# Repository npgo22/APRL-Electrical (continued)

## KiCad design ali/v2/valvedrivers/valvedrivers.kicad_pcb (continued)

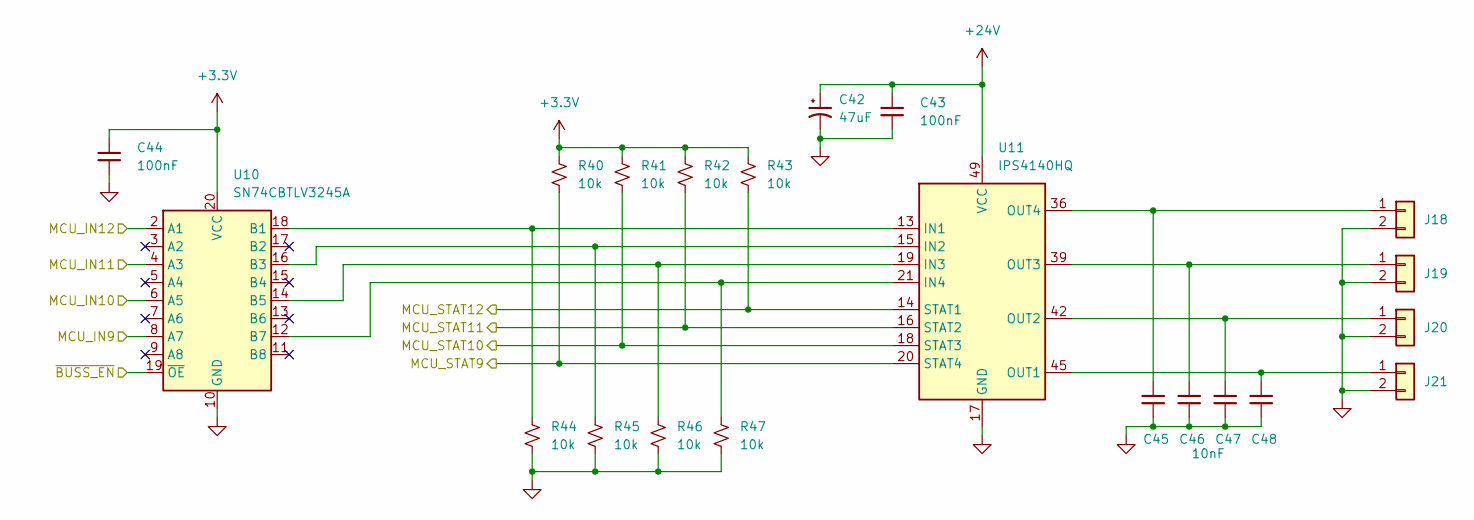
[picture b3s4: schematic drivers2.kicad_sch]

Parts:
C42: 47uF; KEMET MU VIB; MPN A767KS476M1JLAE036
C43, C44: 100nF; C_0603; MPN GRM188R72A104KA35
C45, C46, C47, C48: 10nF; C_0603; MPN GRM1885C1H103JA01
J18, J19, J20, J21: Conn_01x02; Molex_CLIK-Mate_503159-0201_1x02-1MP_P1.50mm_Vertical; MPN 503159-0201
R40, R41, R42, R43, R44, R45, R46, R47: 10k; R_0603; MPN RC0603FR-0710KL
U10: SN74CBTLV3245A; TSSOP-20_4.4x6.5mm_P0.65mm; MPN SN74CBTLV3245APWR
U11: IPS4140HQ; QFN-48_EP_9.01x7.01_Pitch0.5mm; MPN IPS4140HQ

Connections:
+3.3V: C44.1, R40.1, R41.1, R42.1, R43.1, U10.20 (VCC); also elsewhere on the board
+24V: C42.1, C43.1, U11.49 (VCC); also elsewhere on the board
/Driver Set 1/~BUSS_EN: U10.19 (~OE); also elsewhere on the board
/Driver Set 2/MCU_IN9: U10.8 (A7); also elsewhere on the board
/Driver Set 2/MCU_IN10: U10.6 (A5); also elsewhere on the board
/Driver Set 2/MCU_IN11: U10.4 (A3); also elsewhere on the board
/Driver Set 2/MCU_IN12: U10.2 (A1); also elsewhere on the board
/Driver Set 2/MCU_STAT9: R40.2, U11.20 (STAT4); also elsewhere on the board
/Driver Set 2/MCU_STAT10: R41.2, U11.18 (STAT3); also elsewhere on the board
/Driver Set 2/MCU_STAT11: R42.2, U11.16 (STAT2); also elsewhere on the board
/Driver Set 2/MCU_STAT12: R43.2, U11.14 (STAT1); also elsewhere on the board
GND: C42.2, C43.2, C44.2, C45.2, C46.2, C47.2, C48.2, J18.2, J19.2, J20.2, J21.2, R44.2, R45.2, R46.2, R47.2, U10.10 (GND), U11.17 (GND); also elsewhere on the board
unnamed: C45.1, J18.1, U11.36 (OUT4), U11.37 (OUT4), U11.38 (OUT4)
unnamed: C46.1, J19.1, U11.39 (OUT3), U11.40 (OUT3), U11.41 (OUT3)
unnamed: C47.1, J20.1, U11.42 (OUT2), U11.43 (OUT2), U11.44 (OUT2)
unnamed: C48.1, J21.1, U11.45 (OUT1), U11.46 (OUT1), U11.47 (OUT1)
unnamed: R44.1, U10.18 (B1), U11.13 (IN1)
unnamed: R45.1, U10.16 (B3), U11.15 (IN2)
unnamed: R46.1, U10.14 (B5), U11.19 (IN3)
unnamed: R47.1, U10.12 (B7), U11.21 (IN4)

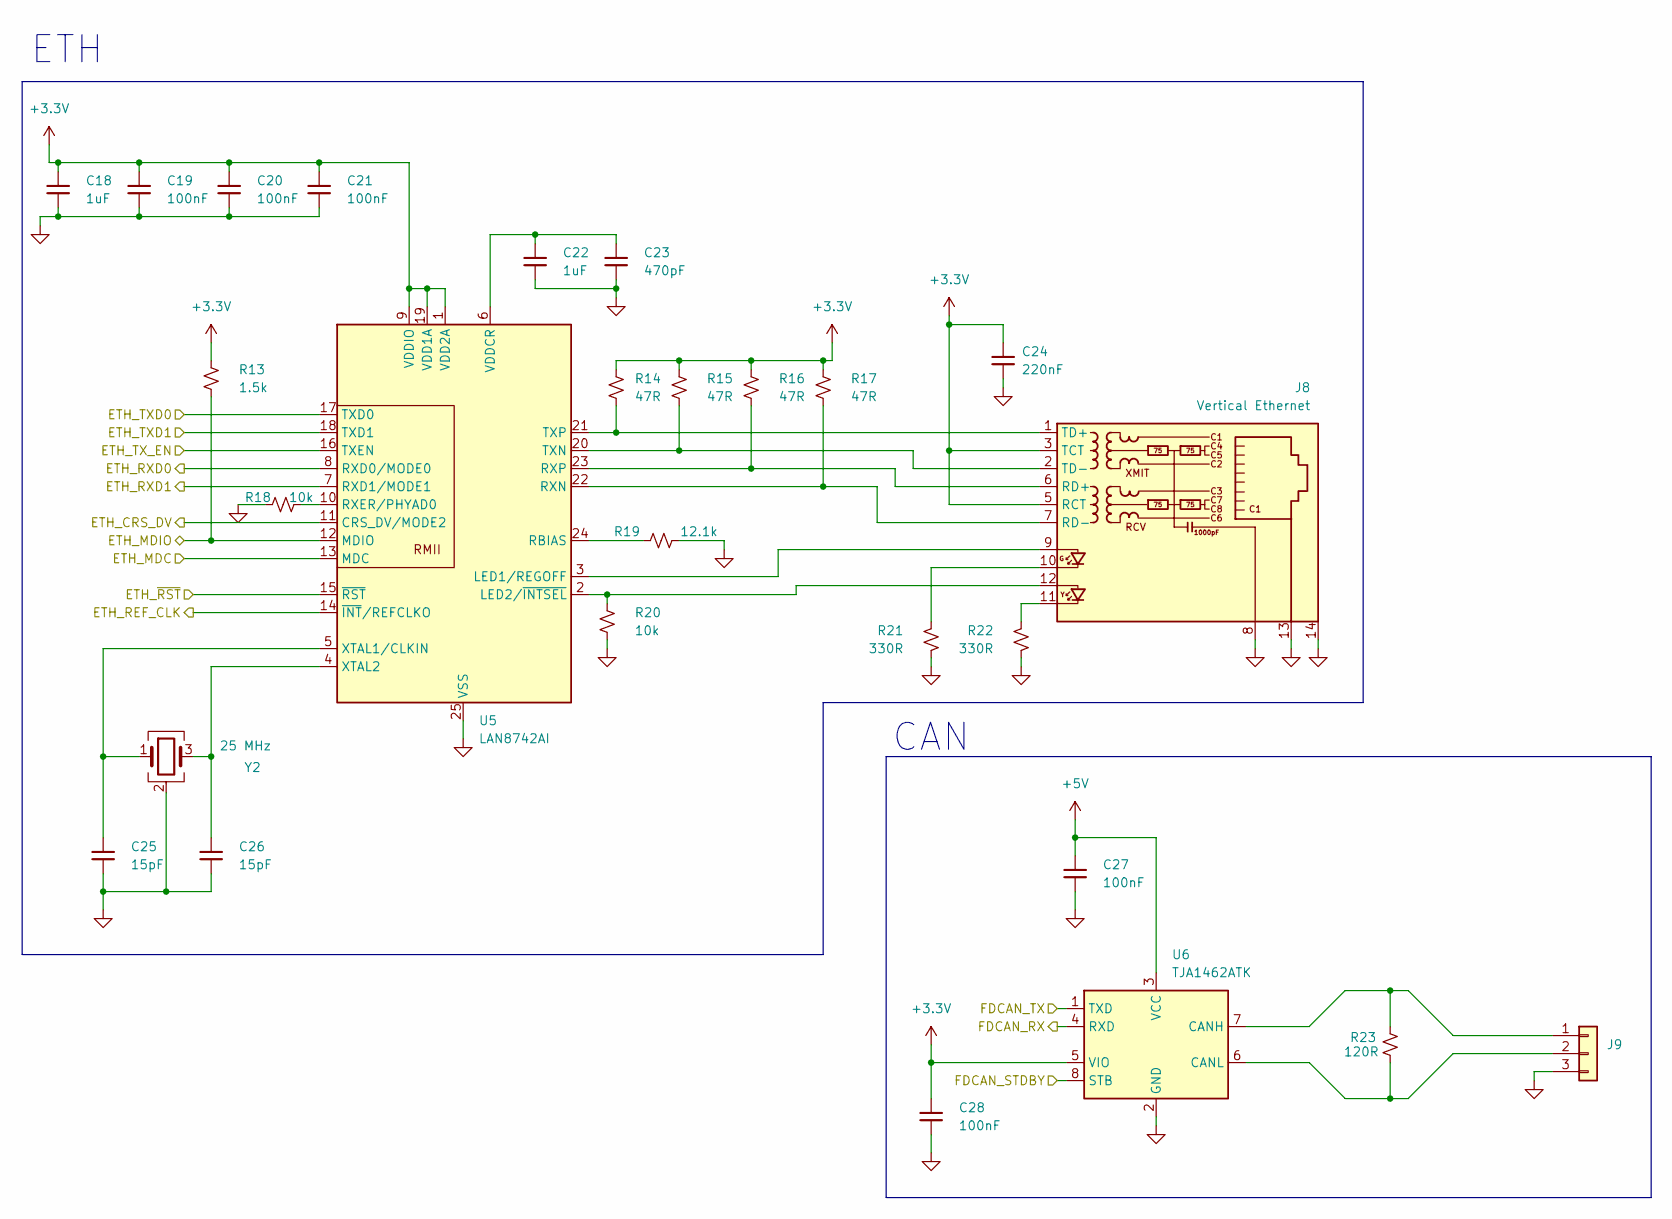
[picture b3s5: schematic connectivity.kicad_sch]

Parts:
C18, C22: 1uF; C_0603; MPN GRM188D72A105KE01
C19, C20, C21, C27, C28: 100nF; C_0603; MPN GRM188R72A104KA35
C23: 470pF; C_0603; MPN GRM1885C1H471JA01
C24: 220nF; C_0603; MPN GRM188R71H224KAC4
C25, C26: 15pF; C_0603; MPN GRM1885C2E150FW07
J8: Vertical Ethernet; RJ45_Hanrun_HY951180A_Vertical; MPN HY951180A
J9: Conn_01x03; Molex_CLIK-Mate_503159-0301_1x03-1MP_P1.50mm_Vertical; MPN 503159-0301
R13: 1.5k; R_0603; MPN RC0603FR-071K5L
R14, R15, R16, R17: 47R; R_0603; MPN RC0603FR-0747RL
R18, R20: 10k; R_0603; MPN RC0603FR-0710KL
R19: 12.1k; R_0603; MPN RT0603BRD0712K1L
R21, R22: 330R; R_0603; MPN RC0603FR-07330RL
R23: 120R; R_0603; MPN AC0603FR-07120RL
U5: LAN8742AI; VQFN-24-1EP_4x4mm_P0.5mm_EP2.5x2.5mm_ThermalVias; MPN LAN8742AI-CZ-TR
U6: TJA1462ATK; HVSON-8-1EP_3x3mm_P0.65mm_EP1.6x2.4mm_ThermalVias; MPN TJA1462ATK/0Z
Y2: 25 MHz; 3225-4P-L; MPN X1E0000210139

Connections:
+3.3V: C18.1, C19.1, C20.1, C21.1, C24.1, C28.1, J8.3 (TCT), J8.5 (RCT), R13.1, R14.1, R15.1, R16.1, R17.1, U5.1 (VDD2A), U5.9 (VDDIO), U5.19 (VDD1A), U6.5 (VIO); also elsewhere on the board
+5V: C27.1, U6.3 (VCC); also elsewhere on the board
/Connectivity/ETH_CRS_DV: U5.11 (CRS_DV/MODE2); also elsewhere on the board
/Connectivity/ETH_MDC: U5.13 (MDC); also elsewhere on the board
/Connectivity/ETH_MDIO: R13.2, U5.12 (MDIO); also elsewhere on the board
/Connectivity/ETH_REF_CLK: U5.14 (~INT/REFCLKO); also elsewhere on the board
/Connectivity/ETH_RXD0: U5.8 (RXD0/MODE0); also elsewhere on the board
/Connectivity/ETH_RXD1: U5.7 (RXD1/MODE1); also elsewhere on the board
/Connectivity/ETH_TXD0: U5.17 (TXD0); also elsewhere on the board
/Connectivity/ETH_TXD1: U5.18 (TXD1); also elsewhere on the board
/Connectivity/ETH_TX_EN: U5.16 (TXEN); also elsewhere on the board
/Connectivity/ETH_~RST: U5.15 (~RST); also elsewhere on the board
/Connectivity/FDCAN_RX: U6.4 (RXD); also elsewhere on the board
/Connectivity/FDCAN_STDBY: U6.8 (STB); also elsewhere on the board
/Connectivity/FDCAN_TX: U6.1 (TXD); also elsewhere on the board
GND: C18.2, C19.2, C20.2, C21.2, C22.2, C23.2, C24.2, C25.2, C26.2, C27.2, C28.2, J8.8, J8.13, J8.14, J9.3, R18.1, R19.2, R20.2, R21.2, R22.2, U5.25 (VSS), U6.2 (GND), U6.9 (GND), Y2.2 (G), Y2.4 (G); also elsewhere on the board
unnamed: J8.10, R21.1
unnamed: J8.11, R22.1
unnamed: J8.6 (RD+), R16.2, U5.23 (RXP)
unnamed: J8.7 (RD-), R17.2, U5.22 (RXN)
unnamed: J8.1 (TD+), R14.2, U5.21 (TXP)
unnamed: J8.2 (TD-), R15.2, U5.20 (TXN)
unnamed: J9.1, R23.2, U6.7 (CANH)
unnamed: J9.2, R23.1, U6.6 (CANL)
unnamed: J8.9, U5.3 (LED1/REGOFF)
unnamed: J8.12, R20.1, U5.2 (LED2/~INTSEL)
unnamed: R19.1, U5.24 (RBIAS)
unnamed: R18.2, U5.10 (RXER/PHYAD0)
unnamed: C22.1, C23.1, U5.6 (VDDCR)
unnamed: C25.1, U5.5 (XTAL1/CLKIN), Y2.1
unnamed: C26.1, U5.4 (XTAL2), Y2.3

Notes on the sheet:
ETH
CAN

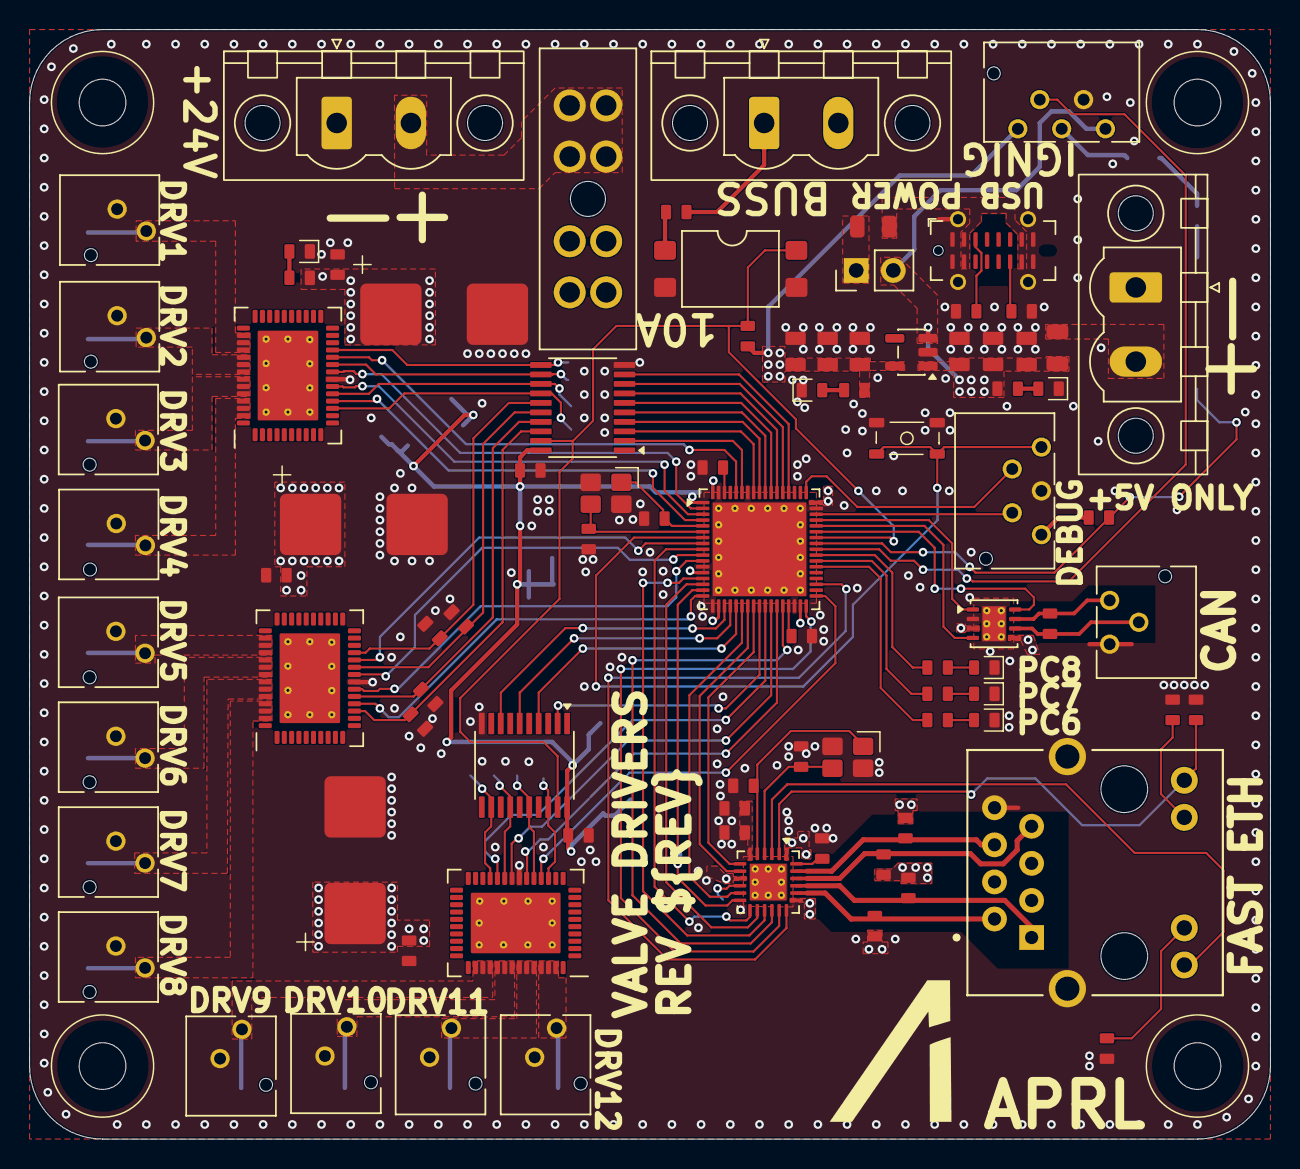
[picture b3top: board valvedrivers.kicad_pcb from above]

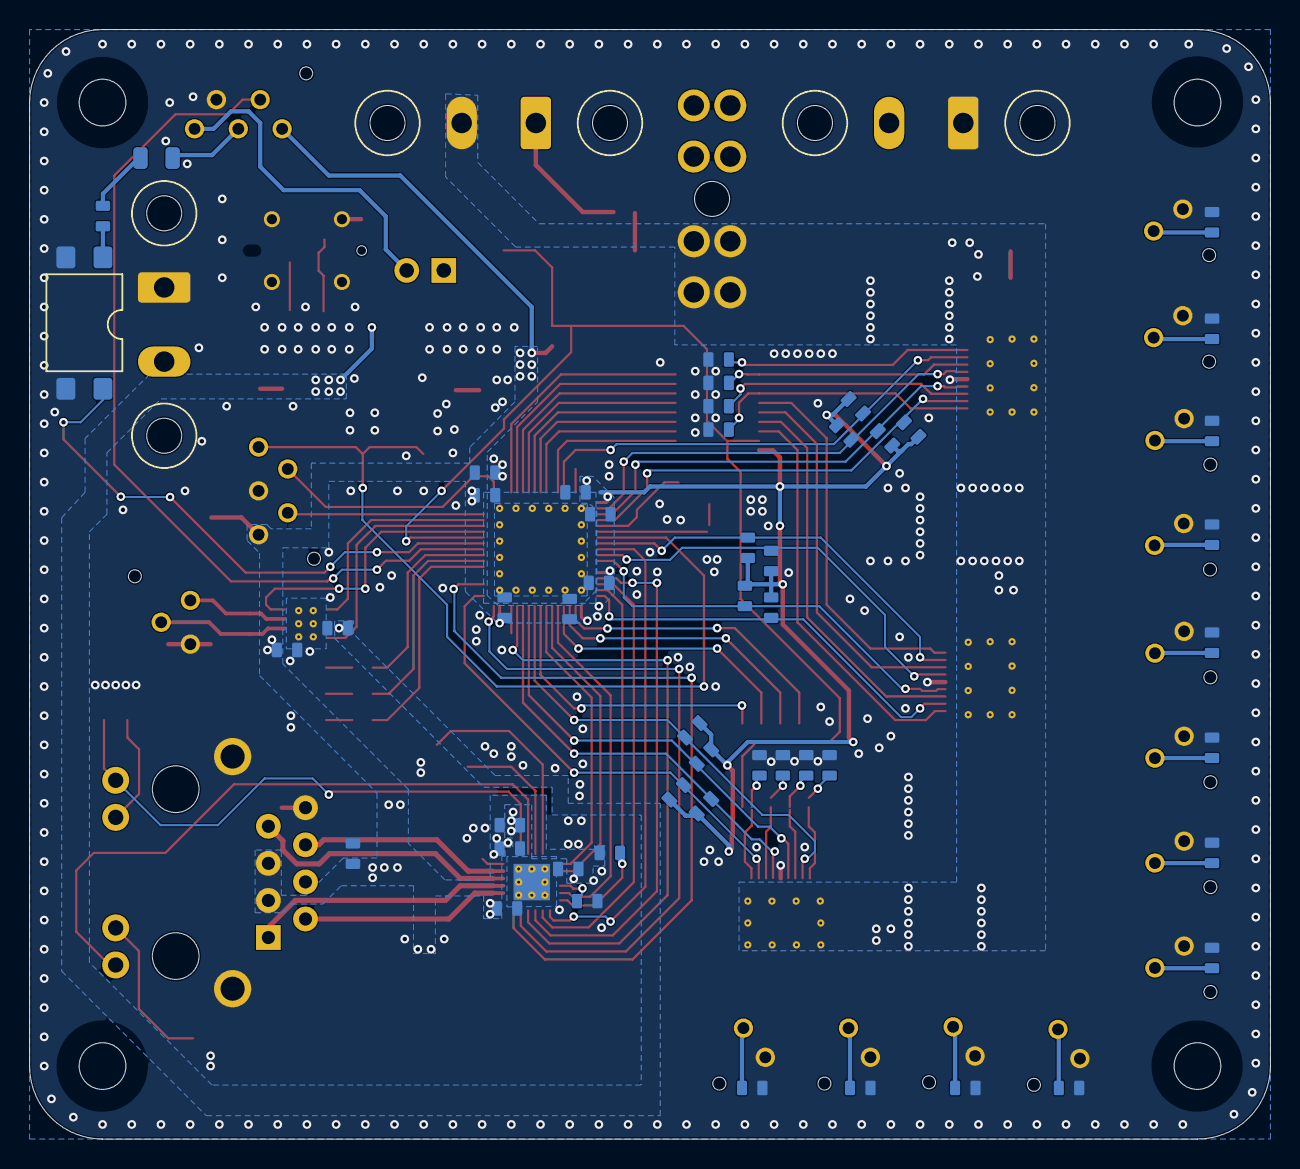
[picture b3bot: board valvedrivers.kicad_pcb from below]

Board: 4 copper layers, 85.0 x 76.0 mm, 144 parts (51 on the bottom side), 110 nets.

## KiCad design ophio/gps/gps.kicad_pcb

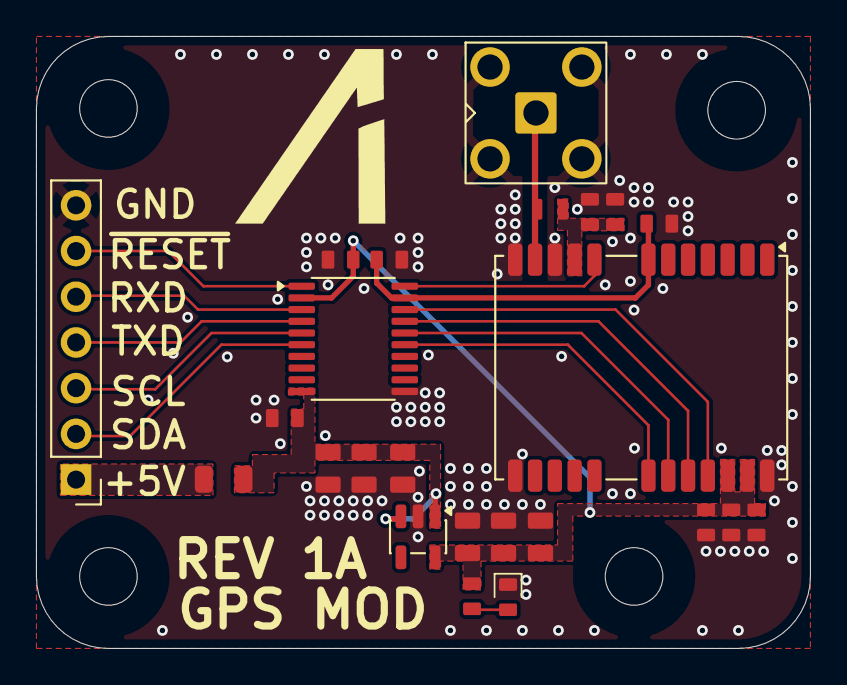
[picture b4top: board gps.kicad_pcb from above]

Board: 4 copper layers, 43.0 x 34.0 mm, 28 parts (0 on the bottom side), 18 nets.

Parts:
C1, C2, C3, C5, C7, C9: 22uF; C_0805
C4, C6, C8, C12, C14: 100nF; C_0603
C10, C11: 33pF; C_0603
C13: 100pF; C_0603
D1: LED_Small; LED_0603
F1: 100mA hold; Fuse_0805_2012Metric
H1, H2, H3, H4: MountingHole; MountingHole_3.2mm_M3
J1: Conn_01x07; PinHeader_1x07_P2.54mm_Vertical
J2: SMA; SMA_BAT_Wireless_BWSMA-KWE-Z001
L1: 68 nH; LQW18AN68NG8Z
R1, R2: 10k; R_0603
U1: AP2112K-3.3; SOT-23-5
U2: TXS0108EPW; TSSOP-20_4.4x6.5mm_P0.65mm
U3: LC29H; ublox_NEO

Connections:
+2.8V: C6.1, C12.1, U2.19 (VCCB), U3.7 (VDD_EXT)
+3.3V: C4.1, C5.1, C7.1, C8.1, C9.1, C10.1, C11.1, R2.1, U1.5 (VOUT), U2.2 (VCCA), U3.22 (V_BCKP), U3.23 (VCC)
+5V: C1.1, C2.1, C3.1, F1.1, R1.1, U1.1 (VIN), U1.3 (EN), U2.10 (OE)
/I2C_SCL: U2.16 (B4), U3.19 (I2C_SCL)
/I2C_SDA: U2.15 (B5), U3.18 (I2C_SDA)
/RXD: U2.18 (B2), U3.21 (RXD)
/TXD: U2.17 (B3), U3.20 (TXD)
/~RESET: U2.20 (B1), U3.8 (~RESET)
GND: C1.2, C2.2, C3.2, C4.2, C5.2, C6.2, C7.2, C8.2, C9.2, C10.2, C11.2, C12.2, C13.2, C14.2, D1.1 (K), J1.7, J2.2 (Ext), R1.2, U1.2 (GND), U2.11 (GND), U3.10 (GND), U3.12 (GND), U3.13 (GND), U3.24 (GND)
unnamed: D1.2 (A), R2.2
unnamed: F1.2, J1.1
unnamed: J1.2, U2.6 (A5)
unnamed: J1.3, U2.5 (A4)
unnamed: J1.4, U2.4 (A3)
unnamed: J1.5, U2.3 (A2)
unnamed: J1.6, U2.1 (A1)
unnamed: J2.1 (In), L1.2, U3.11 (RF_IN)
unnamed: C13.1, C14.1, L1.1, U3.9 (VDD_RF)

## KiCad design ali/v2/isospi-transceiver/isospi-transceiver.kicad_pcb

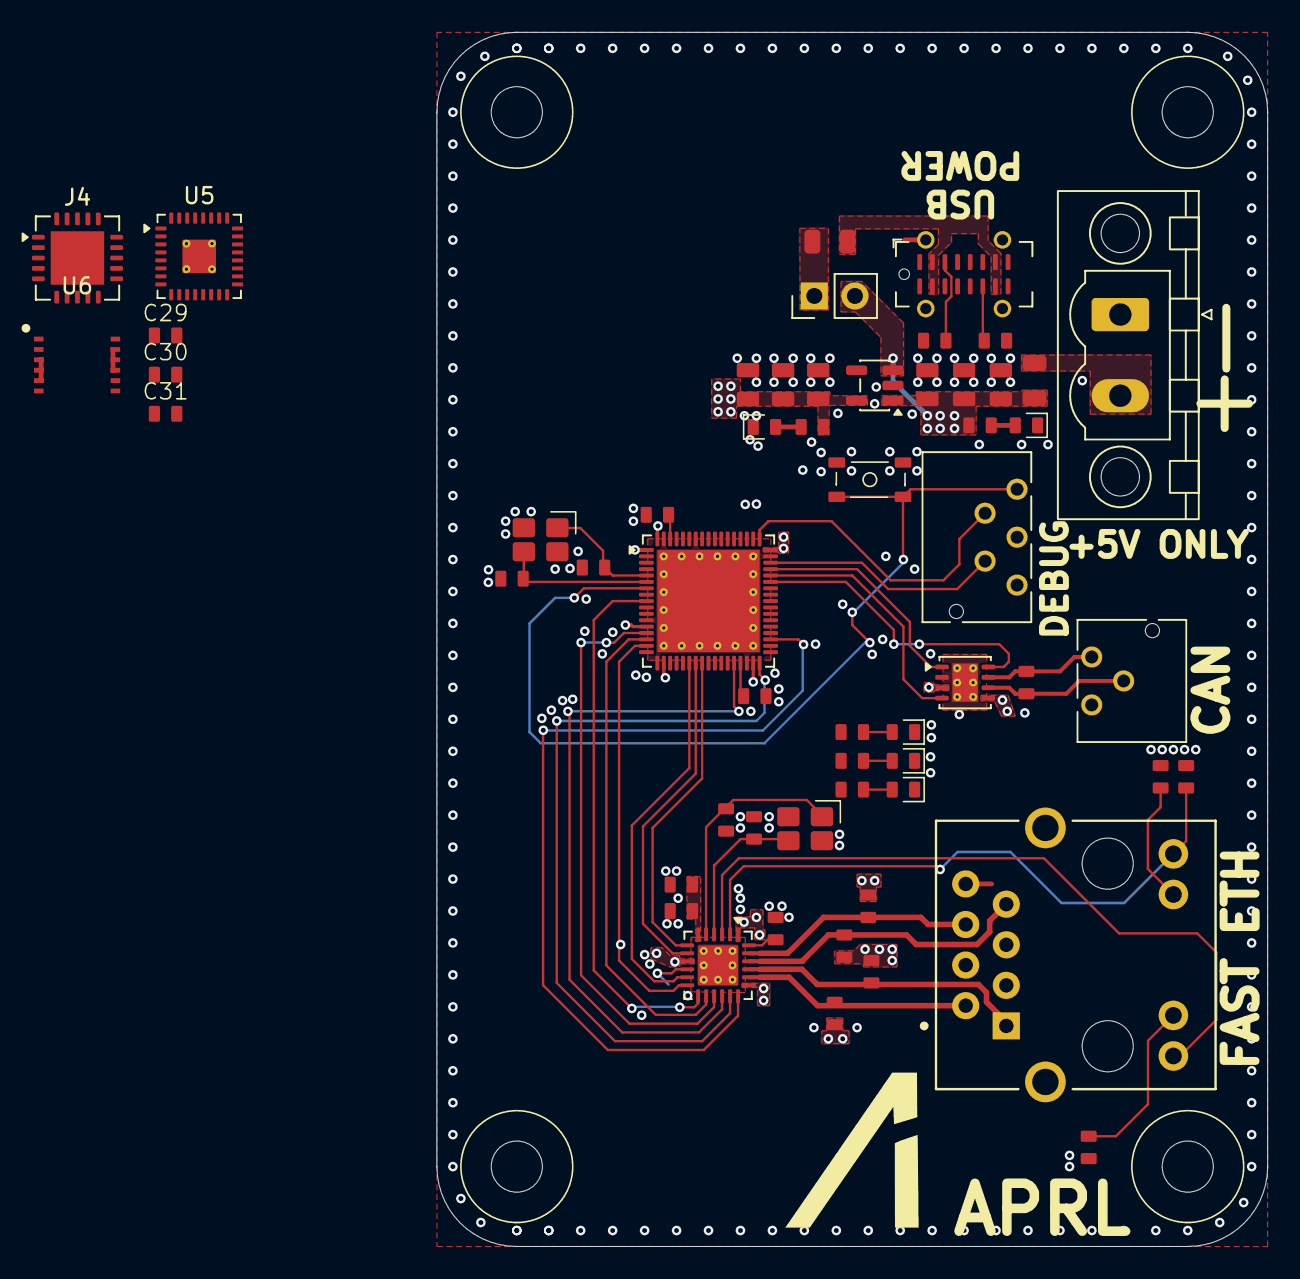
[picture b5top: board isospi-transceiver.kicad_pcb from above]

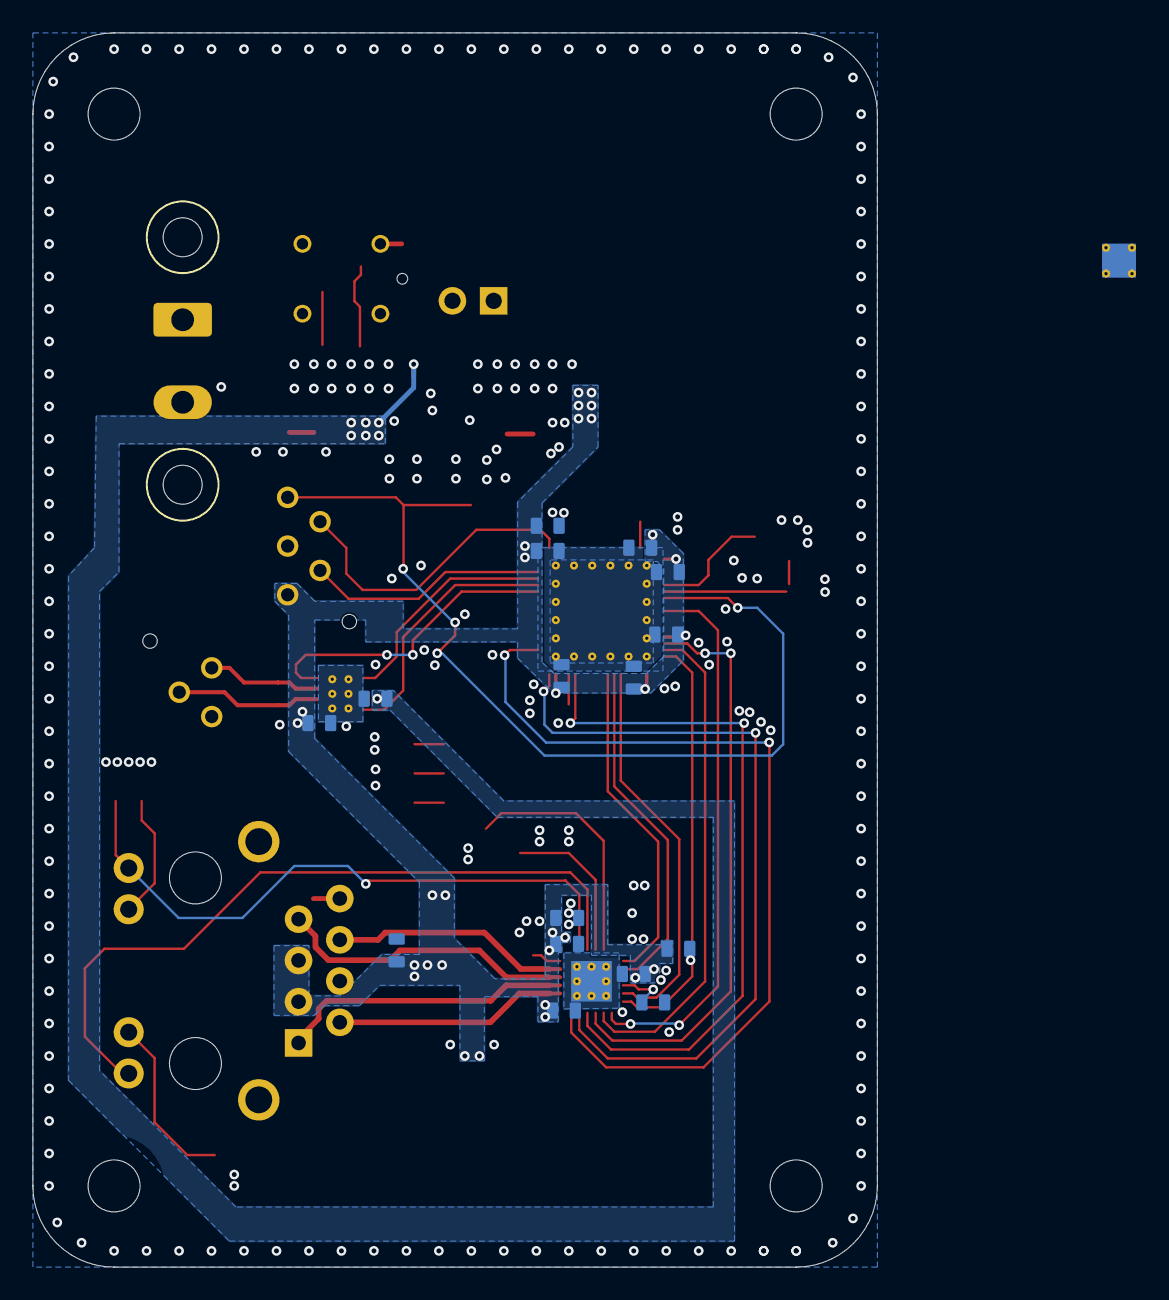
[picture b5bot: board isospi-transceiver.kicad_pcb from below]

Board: 4 copper layers, 52.0 x 76.0 mm, 76 parts (16 on the bottom side), 50 nets.

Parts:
C1, C18, C23: 1uF; C_0603
C2, C3, C4, C5, C6, C7, C19, C20, C21, C22, C25, C29, C30, C31: 100nF; C_0603
C8, C9, C27, C28: 15pF; C_0603
C10, C11: 2.2uF; C_0603
C12, C13, C14, C15, C16, C17: 22uF; C_0805
C24: 470pF; C_0603
C26: 220nF; C_0603
D1, D2, D3, D4, D5: LED; LED_0603
F1, F2: 500mA; Fuse_0805_2012Metric
H1, H2, H3, H4: MountingHole; MountingHole_3.2mm_M3
J1: Conn_02x01; PinHeader_1x02_P2.54mm_Vertical
J2: Conn_01x05; Molex_CLIK-Mate_503159-0501_1x05-1MP_P1.50mm_Vertical
J3: USB_C_Receptacle_USB2.0_16P; USB_C_Receptacle_G-Switch_GT-USB-7051x
J4: Conn_01x06; QFN-20-1EP_5x5mm_P0.65mm_EP3.35x3.35mm
J6: Screw_Terminal_01x02; PhoenixContact_MSTBV_2,5_2-GF-5,08_1x02_P5.08mm_Vertical_Th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
J7: Conn_01x03; Molex_CLIK-Mate_503159-0301_1x03-1MP_P1.50mm_Vertical
J8: Vertical Ethernet; RJ45_Hanrun_HY951180A_Vertical
R1, R2: 5.1k; R_0603
R3, R4, R5, R6, R7, R14, R16: 10k; R_0603
R8: 120R; R_0603
R9: 1.5k; R_0603
R10, R11, R12, R13: 47R; R_0603
R15: 12.1k; R_0603
R17, R18: 330R; R_0603
SW1: SKRPANE010
U1: STM32H563RIV6; QFN-68-1EP_8x8mm_P0.4mm_EP6.4x6.4mm
U2: AP2112K-3.3; SOT-23-5
U3: TJA1462ATK; HVSON-8-1EP_3x3mm_P0.65mm_EP1.6x2.4mm_ThermalVias
U4: LAN8742AI; VQFN-24-1EP_4x4mm_P0.5mm_EP2.5x2.5mm_ThermalVias
U5: ADBMS6821; LFCSP-32-1EP_5x5mm_P0.5mm_EP2.1x2.1mm_ThermalVias
U6: UCC33420-Q1; VSON-12_4x5mm_P0.65mm
Y1, Y2: 25 MHz; 3225-4P-L

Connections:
+3.3V: C1.1, C2.1, C3.1, C4.1, C5.1, C6.1, C7.1, C15.1, C16.1, C17.1, C18.1, C19.1, C20.1, C21.1, C25.1, C26.1, C29.1, J2.1, J8.3 (TCT), J8.5 (RCT), R4.1, R9.1, R10.1, R11.1, R12.1, R13.1, U1.1 (VBAT), U1.13 (VDDA), U1.19 (VDD), U1.33 (VDD), U1.51 (VDD), U1.68 (VDD), U2.5 (VOUT), U3.5 (VIO), U4.1 (VDD2A), U4.9 (VDDIO), U4.19 (VDD1A), U5.1 (MSTR), U5.6 (VDDS)
+5V: C12.1, C13.1, C14.1, C22.1, C30.1, C31.1, F2.2, J1.2, R3.1, U2.1 (VIN), U2.3 (EN), U3.3 (VCC), U5.12 (VDD), U5.13 (VP)
/Connectivity/CAN+: J7.1, R8.2, U3.7 (CANH)
/Connectivity/CAN-: J7.2, R8.1, U3.6 (CANL)
/Connectivity/ETH_CRS_DV: U1.23 (PA7), U4.11 (CRS_DV/MODE2)
/Connectivity/ETH_MDC: U1.9 (PC1), U4.13 (MDC)
/Connectivity/ETH_MDIO: R9.2, U1.16 (PA2), U4.12 (MDIO)
/Connectivity/ETH_REF_CLK: U1.15 (PA1), U4.14 (~INT/REFCLKO)
/Connectivity/ETH_RXD0: U1.24 (PC4), U4.8 (RXD0/MODE0)
/Connectivity/ETH_RXD1: U1.25 (PC5), U4.7 (RXD1/MODE1)
/Connectivity/ETH_TXD0: U1.34 (PB12), U4.17 (TXD0)
/Connectivity/ETH_TXD1: U1.37 (PB15), U4.18 (TXD1)
/Connectivity/ETH_TX_EN: U1.30 (PB11), U4.16 (TXEN)
/Connectivity/ETH_~RST: U1.14 (PA0), U4.15 (~RST)
/Connectivity/FDCAN_RX: U1.47 (PA11), U3.4 (RXD)
/Connectivity/FDCAN_STDBY: U1.46 (PA10), U3.8 (STB)
/Connectivity/FDCAN_TX: U1.48 (PA12), U3.1 (TXD)
/Connectivity/LED1-REGOFF: J8.9, U4.3 (LED1/REGOFF)
/Connectivity/LED2-INTSEL: J8.12, R16.1, U4.2 (LED2/~INTSEL)
/Connectivity/RX+: J8.6 (RD+), R12.2, U4.23 (RXP)
/Connectivity/RX-: J8.7 (RD-), R13.2, U4.22 (RXN)
/Connectivity/TX+: J8.1 (TD+), R10.2, U4.21 (TXP)
/Connectivity/TX-: J8.2 (TD-), R11.2, U4.20 (TXN)
/Microcontroller/SWCLK: J2.4, U1.52 (PA14(JTCK)
/Microcontroller/SWDIO: J2.2, U1.49 (PA13(JTMS)
/Microcontroller/~RST: J2.5, SW1.3 (K), SW1.4 (A), U1.7 (NRST)
GND: C1.2, C2.2, C3.2, C4.2, C5.2, C6.2, C7.2, C8.2, C9.2, C10.2, C11.2, C12.2, C13.2, C14.2, C15.2, C16.2, C17.2, C18.2, C19.2, C20.2, C21.2, C22.2, C23.2, C24.2, C25.2, C26.2, C27.2, C28.2, C29.2, C30.2, C31.2, D1.1 (K), D2.1 (K), D3.1 (K), D4.1 (K), D5.1 (K), J2.3, J3.A1 (GND), J3.A12 (GND), J3.B1 (GND), J3.B12 (GND), J3.SH (SHIELD), J6.1, J7.3, J8.8, J8.13, J8.14, R1.1, R2.2, R14.1, R15.2, R16.2, R17.2, R18.2, SW1.1, SW1.2, U1.12 (VSSA), U1.18 (VSS), U1.32 (VSS), U1.50 (VSS), U1.62 (BOOT0), U1.67 (VSS), U1.69 (VSS), U2.2 (GND), U3.2 (GND), U3.9 (GND), U4.25 (VSS), U5.9 (GND), U5.33 (GND), Y1.2 (G), Y1.4 (G), Y2.2 (G), Y2.4 (G)
unnamed: C10.1, U1.31 (VCAP)
unnamed: C11.1, U1.66 (VCAP)
unnamed: D1.2 (A), R3.2
unnamed: D2.2 (A), R4.2
unnamed: D3.2 (A), R5.1
unnamed: D4.2 (A), R6.1
unnamed: D5.2 (A), R7.1
unnamed: F1.1, J3.A4 (VBUS), J3.A9 (VBUS), J3.B4 (VBUS), J3.B9 (VBUS)
unnamed: F1.2, J1.1
unnamed: J3.A5 (CC1), R2.1
unnamed: J3.B5 (CC2), R1.2
unnamed: F2.1, J6.2
unnamed: J8.10, R17.1
unnamed: J8.11, R18.1
unnamed: C8.1, U1.5 (PH0), Y1.1
unnamed: C9.1, U1.6 (PH1), Y1.3
unnamed: R15.1, U4.24 (RBIAS)
unnamed: R14.2, U4.10 (RXER/PHYAD0)
unnamed: C23.1, C24.1, U4.6 (VDDCR)
unnamed: C27.1, U4.5 (XTAL1/CLKIN), Y2.1
unnamed: C28.1, U4.4 (XTAL2), Y2.3
unnamed: U6.3 (GNDP), U6.4 (GNDP), U6.5 (GNDP), U6.6 (GNDP)
unnamed: U6.9 (GNDS), U6.10 (GNDS), U6.11 (GNDS), U6.12 (GNDS)

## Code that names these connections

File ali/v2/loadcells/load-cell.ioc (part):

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Mcu.Name=STM32H563RIVx
Mcu.Package=VFQFPN68
Mcu.UserName=STM32H563RIVx
PA0.GPIOParameters=GPIO_Label
PA0.GPIO_Label=ETH_nRST
PA0.Signal=GPIO_Output
PA1.GPIOParameters=GPIO_Label
PA1.GPIO_Label=ETH_REF_CLK
PA1.Mode=RMII
PA1.Signal=ETH_REF_CLK
PA10.GPIOParameters=GPIO_Label
PA10.GPIO_Label=FDCAN_STDBY
PA10.Signal=GPIO_Output
PA11.GPIOParameters=GPIO_Label
PA11.GPIO_Label=FDCAN_RX
PA11.Mode=FDCAN_Activate
PA11.Signal=FDCAN1_RX
PA12.GPIOParameters=GPIO_Label
PA12.GPIO_Label=FDCAN_TX
PA12.Mode=FDCAN_Activate
PA12.Signal=FDCAN1_TX
PA13(JTMS/SWDIO).GPIOParameters=GPIO_Label
PA13(JTMS/SWDIO).GPIO_Label=SWDIO
PA13(JTMS/SWDIO).Mode=Serial_Wire
PA13(JTMS/SWDIO).Signal=DEBUG_JTMS-SWDIO
PA14(JTCK/SWCLK).GPIOParameters=GPIO_Label
PA14(JTCK/SWCLK).GPIO_Label=SWCLK
PA14(JTCK/SWCLK).Mode=Serial_Wire
PA14(JTCK/SWCLK).Signal=DEBUG_JTCK-SWCLK
PA15(JTDI).GPIOParameters=GPIO_Label
PA15(JTDI).GPIO_Label=TIM2_CH1
PA15(JTDI).Signal=S_TIM2_CH1
PA2.GPIOParameters=GPIO_Label
PA2.GPIO_Label=ETH_MDIO
PA2.Mode=RMII
PA2.Signal=ETH_MDIO
PA3.GPIOParameters=GPIO_Label
PA3.GPIO_Label=TIM2_CH4
PA3.Signal=S_TIM2_CH4
PA4.Signal=GPIO_Output
PA5.GPIOParameters=GPIO_Label
PA5.GPIO_Label=ADC_SCLK
PA5.Mode=Full_Duplex_Master
PA5.Signal=SPI1_SCK
PA6.Signal=GPIO_Output
PA7.GPIOParameters=GPIO_Label
PA7.GPIO_Label=ETH_CRS_DV
PA7.Mode=RMII
PA7.Signal=ETH_CRS_DV
PB0.Signal=GPIO_Output
PB1.GPIOParameters=GPIO_Label
PB1.GPIO_Label=SENSE_+5V
PB1.Signal=ADCx_INP5
PB10.GPIOParameters=GPIO_Label
PB10.GPIO_Label=TIM2_CH3
PB10.Signal=S_TIM2_CH3
PB11.GPIOParameters=GPIO_Label
PB11.GPIO_Label=ETH_TX_EN
PB11.Mode=RMII
PB11.Signal=ETH_TX_EN
PB12.GPIOParameters=GPIO_Label
PB12.GPIO_Label=ETH_TXD0
PB12.Mode=RMII
PB12.Signal=ETH_TXD0
PB13.Signal=GPIO_Output
PB14.GPIOParameters=GPIO_Label
PB14.GPIO_Label=USER_LED_1
PB14.Signal=GPIO_Output
PB15.GPIOParameters=GPIO_Label
PB15.GPIO_Label=ETH_TXD1
PB15.Mode=RMII
PB15.Signal=ETH_TXD1
PB2.Signal=GPIO_Output
PB3(JTDO/TRACESWO).GPIOParameters=GPIO_Label
PB3(JTDO/TRACESWO).GPIO_Label=ADC_DRDY
PB3(JTDO/TRACESWO).Signal=S_TIM2_CH2
PB4(NJTRST).GPIOParameters=GPIO_Label
PB4(NJTRST).GPIO_Label=ADC_MISO
PB4(NJTRST).Mode=Full_Duplex_Master
PB4(NJTRST).Signal=SPI1_MISO
PB5.GPIOParameters=GPIO_Label
PB5.GPIO_Label=ADC_MOSI
PB5.Mode=Full_Duplex_Master
PB5.Signal=SPI1_MOSI
PB6.GPIOParameters=GPIO_Label
PB6.GPIO_Label=I2C1_SCL
PB6.Mode=I2C
PB6.Signal=I2C1_SCL
PB7.GPIOParameters=GPIO_Label
PB7.GPIO_Label=I2C1_SCA
PB7.Mode=I2C
PB7.Signal=I2C1_SDA
PB8.GPIOParameters=GPIO_Label
PB8.GPIO_Label=UART4_RX
PB8.Mode=Asynchronous
PB8.Signal=UART4_RX
PB9.GPIOParameters=GPIO_Label
PB9.GPIO_Label=UART4_TX
PB9.Mode=Asynchronous
PB9.Signal=UART4_TX
PC0.GPIOParameters=GPIO_Label
PC0.GPIO_Label=CJC_nRESET
PC0.Signal=GPIO_Output
PC1.GPIOParameters=GPIO_Label
PC1.GPIO_Label=ETH_MDC
PC1.Mode=RMII
PC1.Signal=ETH_MDC
PC12.GPIOParameters=GPIO_Label
PC12.GPIO_Label=ADC_RESET
PC12.Signal=GPIO_Output
PC13.GPIOParameters=GPIO_Label
PC13.GPIO_Label=ADC_CS
PC13.Signal=GPIO_Output
PC14-OSC32_IN(OSC32_IN).GPIOParameters=GPIO_Label
PC14-OSC32_IN(OSC32_IN).GPIO_Label=ADC_START
PC14-OSC32_IN(OSC32_IN).Signal=GPIO_Output
PC2.Signal=GPIO_Output
PC3.Signal=GPIO_Output
PC4.GPIOParameters=GPIO_Label
PC4.GPIO_Label=ETH_RXD0
PC4.Mode=RMII
PC4.Signal=ETH_RXD0
PC5.GPIOParameters=GPIO_Label
PC5.GPIO_Label=ETH_RXD1
PC5.Mode=RMII
PC5.Signal=ETH_RXD1
PC6.GPIOParameters=GPIO_Label
PC6.GPIO_Label=USER_LED_3
PC6.Signal=GPIO_Output
PC9.Signal=GPIO_Output
PD12.GPIOParameters=GPIO_Label
PD12.GPIO_Label=USER_LED_2
PD12.Signal=GPIO_Output
PH0-OSC_IN(PH0).Mode=HSE-External-Oscillator
PH0-OSC_IN(PH0).Signal=RCC_OSC_IN
PH1-OSC_OUT(PH1).Mode=HSE-External-Oscillator
PH1-OSC_OUT(PH1).Signal=RCC_OSC_OUT
RCC.HSE_VALUE=25000000
RCC.SYSCLKFreq_VALUE=32000000
board=custom

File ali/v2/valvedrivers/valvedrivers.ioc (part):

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Mcu.Name=STM32H563RIVx
Mcu.Package=VFQFPN68
Mcu.UserName=STM32H563RIVx
PA0.GPIOParameters=GPIO_Label
PA0.GPIO_Label=ETH_nRST
PA0.Signal=GPIO_Output
PA1.Mode=RMII
PA1.Signal=ETH_REF_CLK
PA10.GPIOParameters=GPIO_Label
PA10.GPIO_Label=FDCAN_STDBY
PA10.Signal=GPIO_Output
PA11.Mode=FDCAN_Activate
PA11.Signal=FDCAN1_RX
PA12.Mode=FDCAN_Activate
PA12.Signal=FDCAN1_TX
PA13(JTMS/SWDIO).Mode=Serial_Wire
PA13(JTMS/SWDIO).Signal=DEBUG_JTMS-SWDIO
PA14(JTCK/SWCLK).Mode=Serial_Wire
PA14(JTCK/SWCLK).Signal=DEBUG_JTCK-SWCLK
PA2.Mode=RMII
PA2.Signal=ETH_MDIO
PA3.GPIOParameters=GPIO_Label
PA3.GPIO_Label=DRV1_4_IN
PA3.Signal=GPIO_Output
PA4.GPIOParameters=GPIO_Label
PA4.GPIO_Label=DRV1_3_IN
PA4.Signal=GPIO_Output
PA5.GPIOParameters=GPIO_Label
PA5.GPIO_Label=DRV1_2_IN
PA5.Signal=GPIO_Output
PA6.GPIOParameters=GPIO_Label
PA6.GPIO_Label=DRV1_1_IN
PA6.Signal=GPIO_Output
PA7.Mode=RMII
PA7.Signal=ETH_CRS_DV
PA9.GPIOParameters=GPIO_PuPd,GPIO_Label
PA9.GPIO_Label=PWR_STAT
PA9.GPIO_PuPd=GPIO_PULLDOWN
PA9.Signal=GPIO_Input
PB0.GPIOParameters=GPIO_Label
PB0.GPIO_Label=DRV2_4_IN
PB0.Signal=GPIO_Output
PB1.GPIOParameters=GPIO_Label
PB1.GPIO_Label=DRV2_3_IN
PB1.Signal=GPIO_Output
PB10.GPIOParameters=GPIO_Label
PB10.GPIO_Label=DRV2_1_IN
PB10.Signal=GPIO_Output
PB11.Mode=RMII
PB11.Signal=ETH_TX_EN
PB12.Mode=RMII
PB12.Signal=ETH_TXD0
PB13.GPIOParameters=GPIO_Label
PB13.GPIO_Label=DRV3_4_IN
PB13.Signal=GPIO_Output
PB14.GPIOParameters=GPIO_Label
PB14.GPIO_Label=DRV3_3_IN
PB14.Signal=GPIO_Output
PB15.Mode=RMII
PB15.Signal=ETH_TXD1
PB2.GPIOParameters=GPIO_Label
PB2.GPIO_Label=DRV2_2_IN
PB2.Signal=GPIO_Output
PB3(JTDO/TRACESWO).GPIOParameters=GPIO_PuPd,GPIO_Label
PB3(JTDO/TRACESWO).GPIO_Label=DRV1_2_STAT
PB3(JTDO/TRACESWO).GPIO_PuPd=GPIO_PULLDOWN
PB3(JTDO/TRACESWO).Signal=GPIO_Input
PB4(NJTRST).GPIOParameters=GPIO_PuPd,GPIO_Label
PB4(NJTRST).GPIO_Label=DRV1_1_STAT
PB4(NJTRST).GPIO_PuPd=GPIO_PULLDOWN
PB4(NJTRST).Signal=GPIO_Input
PB5.GPIOParameters=GPIO_PuPd,GPIO_Label
PB5.GPIO_Label=DRV2_4_STAT
PB5.GPIO_PuPd=GPIO_PULLDOWN
PB5.Signal=GPIO_Input
PB6.GPIOParameters=GPIO_PuPd,GPIO_Label
PB6.GPIO_Label=DRV2_3_STAT
PB6.GPIO_PuPd=GPIO_PULLDOWN
PB6.Signal=GPIO_Input
PB7.GPIOParameters=GPIO_PuPd,GPIO_Label
PB7.GPIO_Label=DRV2_2_STAT
PB7.GPIO_PuPd=GPIO_PULLDOWN
PB7.Signal=GPIO_Input
PB8.GPIOParameters=GPIO_PuPd,GPIO_Label
PB8.GPIO_Label=DRV2_1_STAT
PB8.GPIO_PuPd=GPIO_PULLDOWN
PB8.Signal=GPIO_Input
PB9.GPIOParameters=GPIO_PuPd,GPIO_Label
PB9.GPIO_Label=DRV3_4_STAT
PB9.GPIO_PuPd=GPIO_PULLDOWN
PB9.Signal=GPIO_Input
PC0.GPIOParameters=GPIO_PuPd,GPIO_Label
PC0.GPIO_Label=DRV3_1_STAT
PC0.GPIO_PuPd=GPIO_PULLDOWN
PC0.Signal=GPIO_Input
PC1.Mode=RMII
PC1.Signal=ETH_MDC
PC11.GPIOParameters=GPIO_PuPd,GPIO_Label
PC11.GPIO_Label=DRV1_4_STAT
PC11.GPIO_PuPd=GPIO_PULLDOWN
PC11.Signal=GPIO_Input
PC12.GPIOParameters=GPIO_PuPd,GPIO_Label
PC12.GPIO_Label=DRV1_3_STAT
PC12.GPIO_PuPd=GPIO_PULLDOWN
PC12.Signal=GPIO_Input
PC14-OSC32_IN(OSC32_IN).GPIOParameters=GPIO_PuPd,GPIO_Label
PC14-OSC32_IN(OSC32_IN).GPIO_Label=DRV3_3_STAT
PC14-OSC32_IN(OSC32_IN).GPIO_PuPd=GPIO_PULLDOWN
PC14-OSC32_IN(OSC32_IN).Signal=GPIO_Input
PC15-OSC32_OUT(OSC32_OUT).GPIOParameters=GPIO_PuPd,GPIO_Label
PC15-OSC32_OUT(OSC32_OUT).GPIO_Label=DRV3_2_STAT
PC15-OSC32_OUT(OSC32_OUT).GPIO_PuPd=GPIO_PULLDOWN
PC15-OSC32_OUT(OSC32_OUT).Signal=GPIO_Input
PC4.Mode=RMII
PC4.Signal=ETH_RXD0
PC5.Mode=RMII
PC5.Signal=ETH_RXD1
PC6.GPIOParameters=GPIO_Label
PC6.GPIO_Label=USER_LED_1
PC6.Signal=GPIO_Output
PC7.GPIOParameters=GPIO_Label
PC7.GPIO_Label=USER_LED_2
PC7.Signal=GPIO_Output
PC8.GPIOParameters=GPIO_Label
PC8.GPIO_Label=USER_LED_3
PC8.Signal=GPIO_Output
PD11.GPIOParameters=GPIO_Label
PD11.GPIO_Label=DRV3_2_IN
PD11.Signal=GPIO_Output
PD12.GPIOParameters=GPIO_Label
PD12.GPIO_Label=DRV3_1_IN
PD12.Signal=GPIO_Output
PH0-OSC_IN(PH0).Mode=HSE-External-Oscillator
PH0-OSC_IN(PH0).Signal=RCC_OSC_IN
PH1-OSC_OUT(PH1).Mode=HSE-External-Oscillator
PH1-OSC_OUT(PH1).Signal=RCC_OSC_OUT
RCC.HSE_VALUE=25000000
RCC.SYSCLKFreq_VALUE=250000000
RCC.SYSCLKSource=RCC_SYSCLKSOURCE_PLLCLK
board=custom
